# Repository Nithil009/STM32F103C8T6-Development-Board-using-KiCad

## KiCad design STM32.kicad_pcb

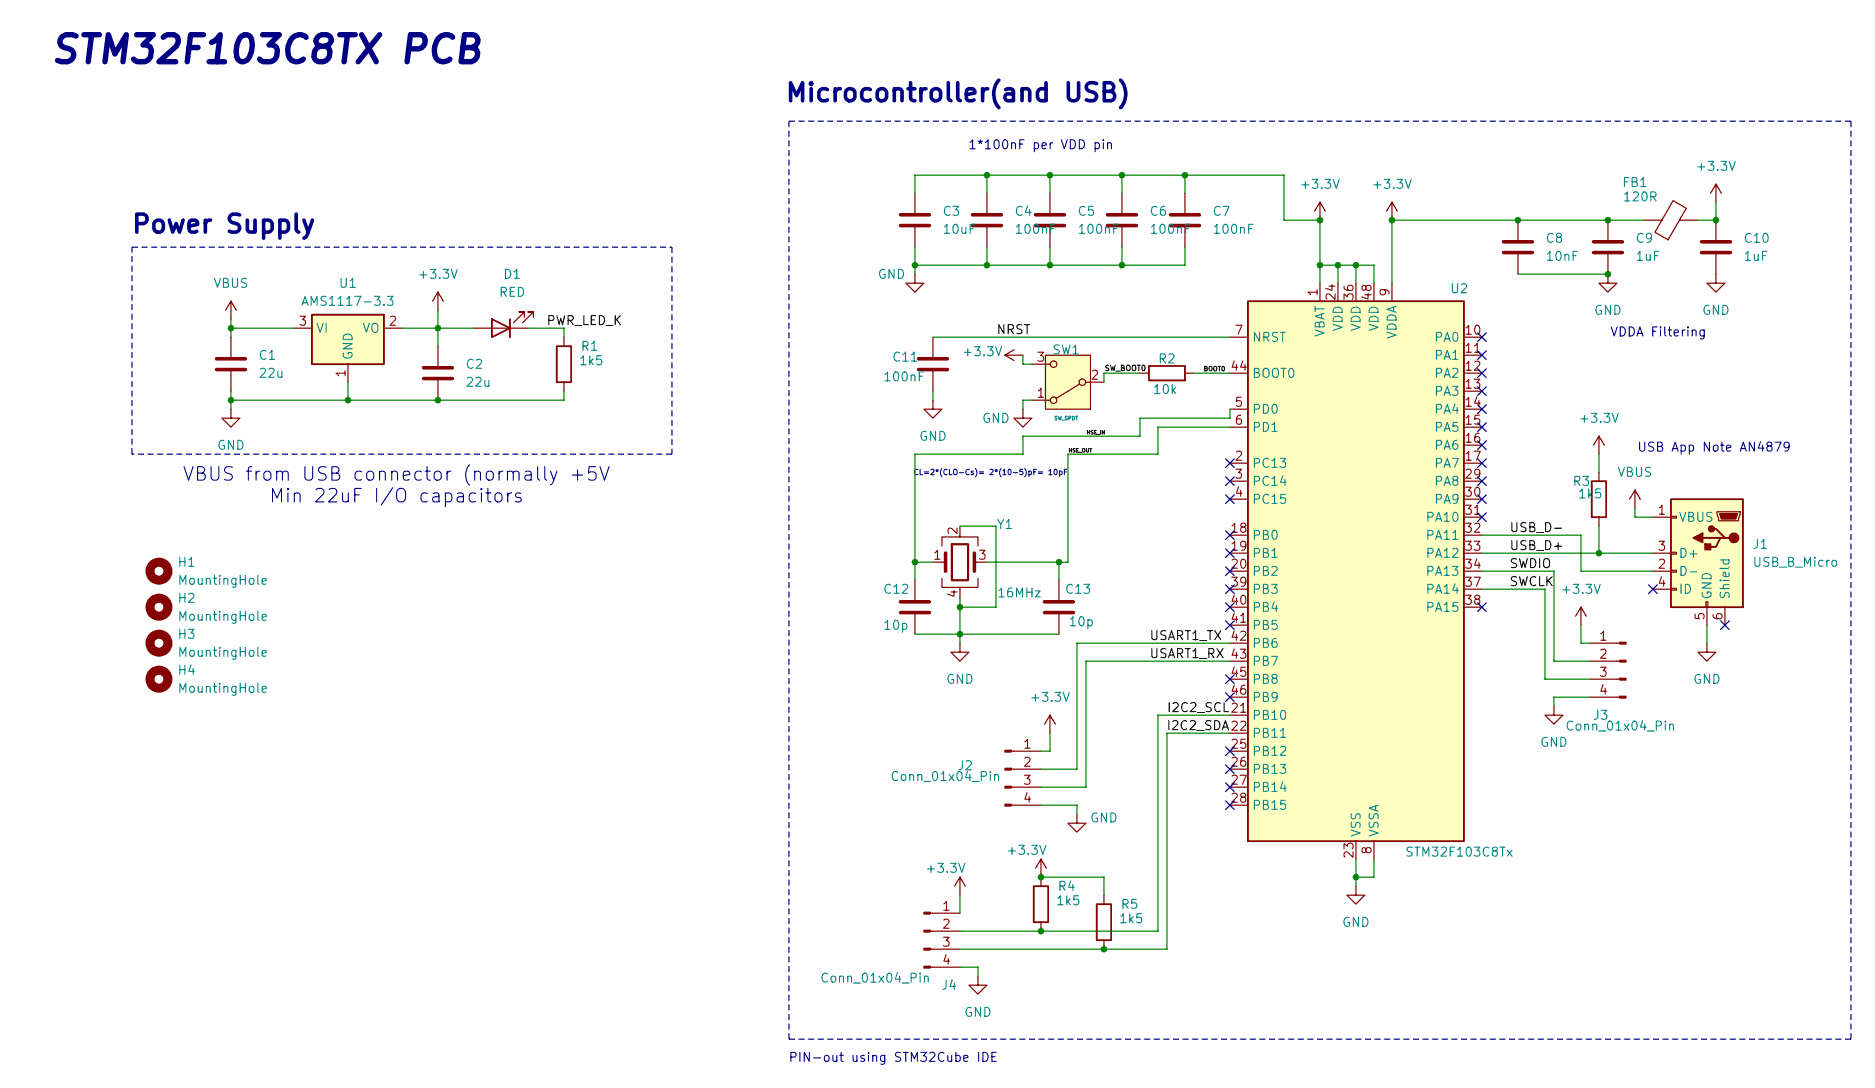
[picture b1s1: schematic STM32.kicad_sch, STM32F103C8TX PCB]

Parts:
C1, C2: 22u; C_0805_2012Metric
C3: 10uF; C_0603_1608Metric
C4, C5, C6, C7, C11: 100nF; C_0402_1005Metric
C8: 10nF; C_0402_1005Metric
C9, C10: 1uF; C_0402_1005Metric
C12, C13: 10p; C_0402_1005Metric
D1: RED; LED_0603_1608Metric
FB1: 120R; R_0402_1005Metric
H1, H2, H3, H4: MountingHole; MountingHole_2.2mm_M2
J1: USB_B_Micro; USB_Micro-B_Wuerth_629105150521
J2, J3, J4: Conn_01x04_Pin; PinHeader_1x04_P2.54mm_Vertical
R1, R3, R4, R5: 1k5; C_0402_1005Metric
R2: 10k; C_0402_1005Metric
SW1: SW_SPDT; SW_SPDT_PCM12
U1: AMS1117-3.3; SOT-223-3_TabPin2
U2: STM32F103C8Tx; LQFP-48_7x7mm_P0.5mm
Y1: 16MHz; Crystal_SMD_3225-4Pin_3.2x2.5mm

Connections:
+3.3V: C2.1, C3.1, C4.1, C5.1, C6.1, C7.1, C8.1, C9.1, C10.1, D1.2 (A), FB1.1, FB1.2, J2.1, J3.1, J4.1, R3.1, R4.1, R5.1, SW1.3 (C), U1.2 (VO), U2.1 (VBAT), U2.9 (VDDA), U2.24 (VDD), U2.36 (VDD), U2.48 (VDD)
/BOOT0: R2.2, U2.44 (BOOT0)
/HSE_IN: C12.1, U2.5 (PD0), Y1.1
/HSE_OUT: C13.1, U2.6 (PD1), Y1.3
/I2C2_SCL: J4.2, R4.2, U2.21 (PB10)
/I2C2_SDA: J4.3, R5.2, U2.22 (PB11)
/NRST: C11.1, U2.7 (NRST)
/PWR_LED_K: D1.1 (K), R1.1
/SWCLK: J3.3, U2.37 (PA14)
/SWDIO: J3.2, U2.34 (PA13)
/SW_BOOT0: R2.1, SW1.2 (B)
/USART1_RX: J2.3, U2.43 (PB7)
/USART1_TX: J2.2, U2.42 (PB6)
/USB_D+: J1.3 (D+), R3.2, U2.33 (PA12)
/USB_D-: J1.2 (D-), U2.32 (PA11)
GND: C1.2, C2.2, C3.2, C4.2, C5.2, C6.2, C7.2, C8.2, C9.2, C10.2, C11.2, C12.2, C13.2, J1.5 (GND), J2.4, J3.4, J4.4, R1.2, SW1.1 (A), U1.1 (GND), U2.8 (VSSA), U2.23 (VSS), U2.35 (VSS), U2.47 (VSS), Y1.2, Y1.4
VBUS: C1.1, J1.1 (VBUS), U1.3 (VI)

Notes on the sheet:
PIN-out using STM32Cube IDE
1*100nF per VDD pin
Power Supply
CL=2*(CLO-Cs)= 2*(10-5)pF= 10pF
STM32F103C8TX PCB
Microcontroller(and USB)
USB App Note AN4879
VBUS from USB connector (normally +5V Min 22uF I/O capacitors
VDDA Filtering

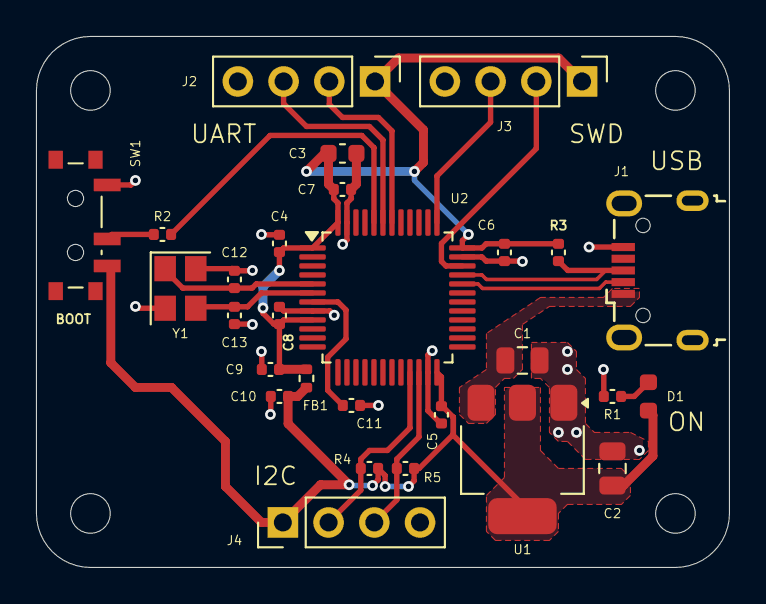
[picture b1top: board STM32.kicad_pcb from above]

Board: 2 copper layers, 38.5 x 29.5 mm, 32 parts (0 on the bottom side), 17 nets.

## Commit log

2025-08-12 README.md
